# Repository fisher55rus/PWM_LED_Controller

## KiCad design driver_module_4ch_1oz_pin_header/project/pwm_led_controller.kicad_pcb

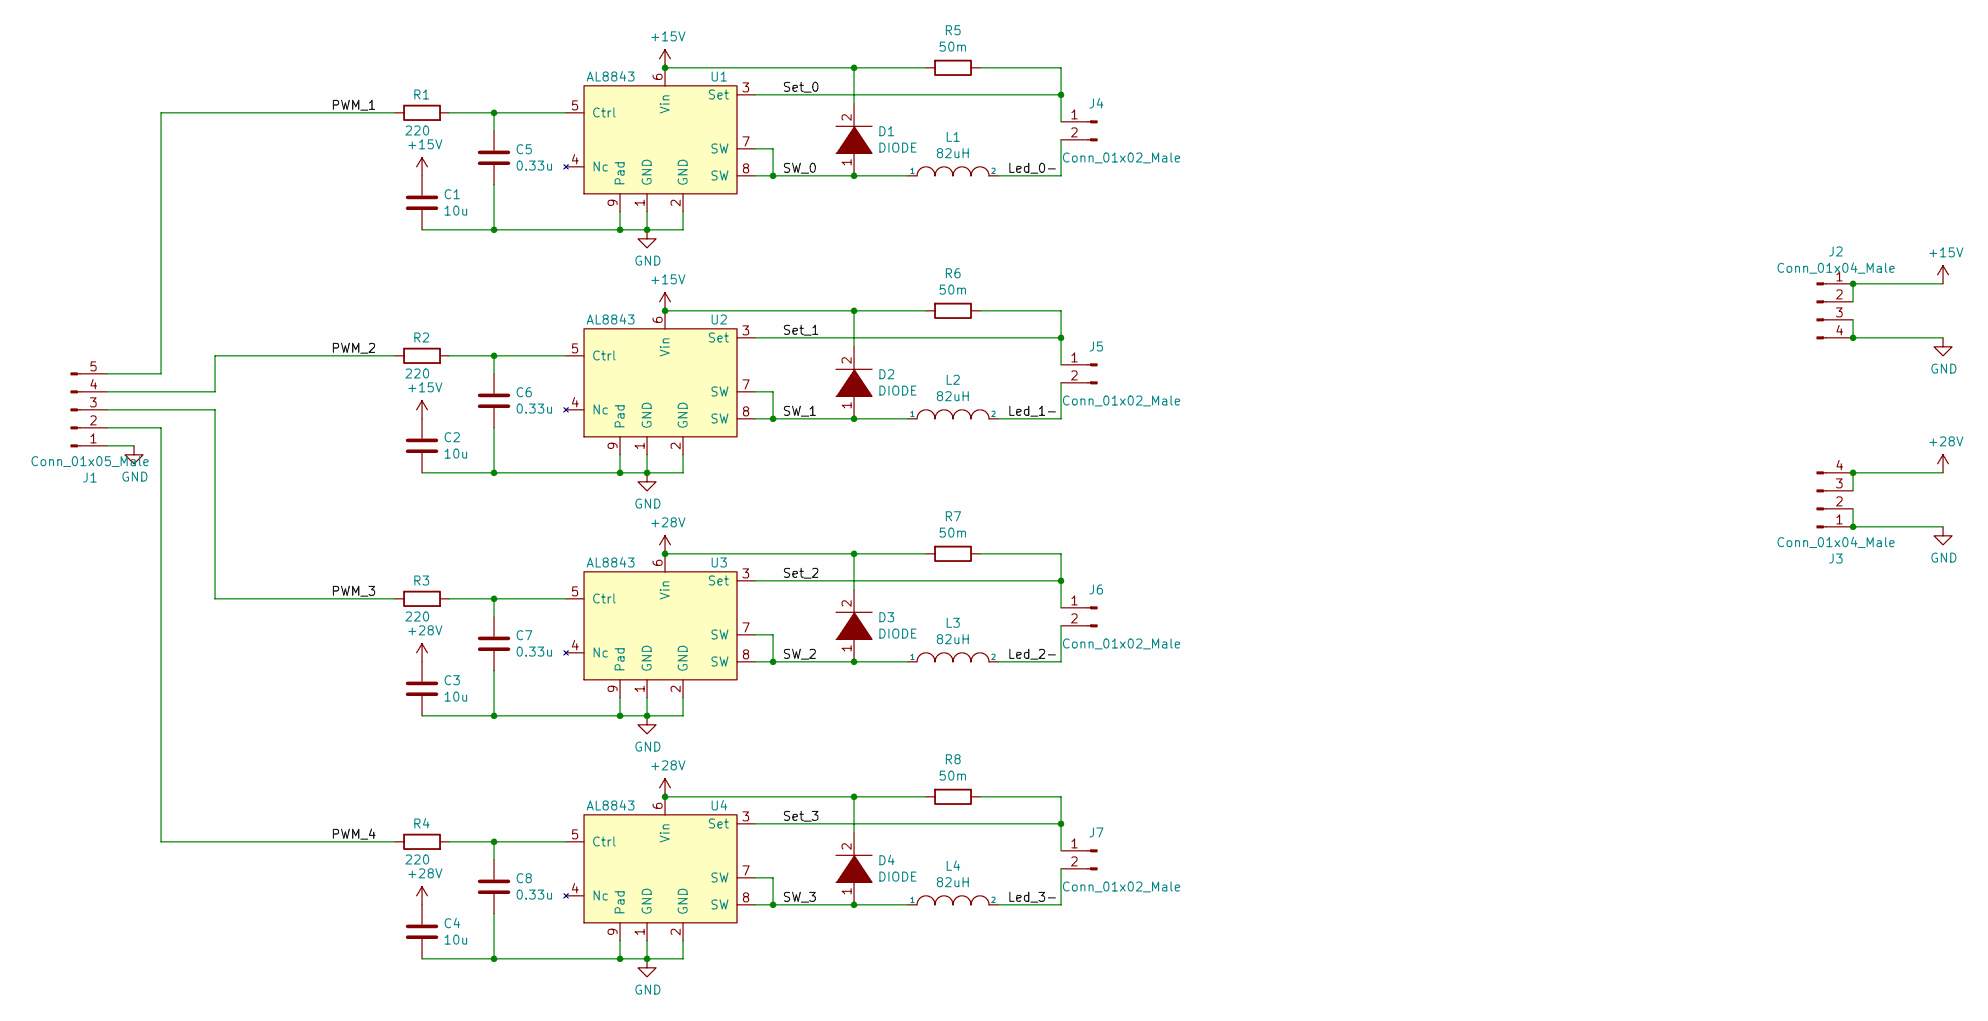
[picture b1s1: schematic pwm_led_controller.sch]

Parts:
C1, C2, C3, C4: 10u; C_1206_3216Metric_Pad1.42x1.75mm_HandSolder
C5, C6, C7, C8: 0.33u; C_0603_1608Metric_Pad1.05x0.95mm_HandSolder
D1, D2, D3, D4: DIODE; D_SMB_Handsoldering
J1: Conn_01x05_Male; PinHeader_1x05_P2.54mm_Vertical
J2, J3: Conn_01x04_Male; PinHeader_1x04_P2.54mm_Vertical
J4, J5, J6, J7: Conn_01x02_Male; PinHeader_1x02_P2.54mm_Vertical
L1, L2, L3, L4: 82uH; Package_2-smd_10.7x10mm
R1, R2, R3, R4: 220; R_0603_1608Metric_Pad1.05x0.95mm_HandSolder
R5, R6, R7, R8: 50m; R_1210_3225Metric_Pad1.42x2.65mm_HandSolder
U1, U2, U3, U4: AL8843; Diodes_PSOP-8

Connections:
+15V: C1.1, C2.1, D1.2 (A), D2.2 (A), J2.1, J2.2, R5.2, R6.2, U1.6 (Vin), U2.6 (Vin)
+28V: C3.1, C4.1, D3.2 (A), D4.2 (A), J3.3, J3.4, R7.2, R8.2, U3.6 (Vin), U4.6 (Vin)
/Led_0-: J4.2, L1.2
/Led_1-: J5.2, L2.2
/Led_2-: J6.2, L3.2
/Led_3-: J7.2, L4.2
/PWM_1: J1.5, R1.1
/PWM_2: J1.4, R2.1
/PWM_3: J1.3, R3.1
/PWM_4: J1.2, R4.1
/SW_0: D1.1 (K), L1.1, U1.7 (SW), U1.8 (SW)
/SW_1: D2.1 (K), L2.1, U2.7 (SW), U2.8 (SW)
/SW_2: D3.1 (K), L3.1, U3.7 (SW), U3.8 (SW)
/SW_3: D4.1 (K), L4.1, U4.7 (SW), U4.8 (SW)
/Set_0: J4.1, R5.1, U1.3 (Set)
/Set_1: J5.1, R6.1, U2.3 (Set)
/Set_2: J6.1, R7.1, U3.3 (Set)
/Set_3: J7.1, R8.1, U4.3 (Set)
GND: C1.2, C2.2, C3.2, C4.2, C5.2, C6.2, C7.2, C8.2, J1.1, J2.3, J2.4, J3.1, J3.2, U1.1 (GND), U1.2 (GND), U1.9 (Pad), U2.1 (GND), U2.2 (GND), U2.9 (Pad), U3.1 (GND), U3.2 (GND), U3.9 (Pad), U4.1 (GND), U4.2 (GND), U4.9 (Pad)
unnamed: C5.1, R1.2, U1.5 (Ctrl)
unnamed: C6.1, R2.2, U2.5 (Ctrl)
unnamed: C7.1, R3.2, U3.5 (Ctrl)
unnamed: C8.1, R4.2, U4.5 (Ctrl)

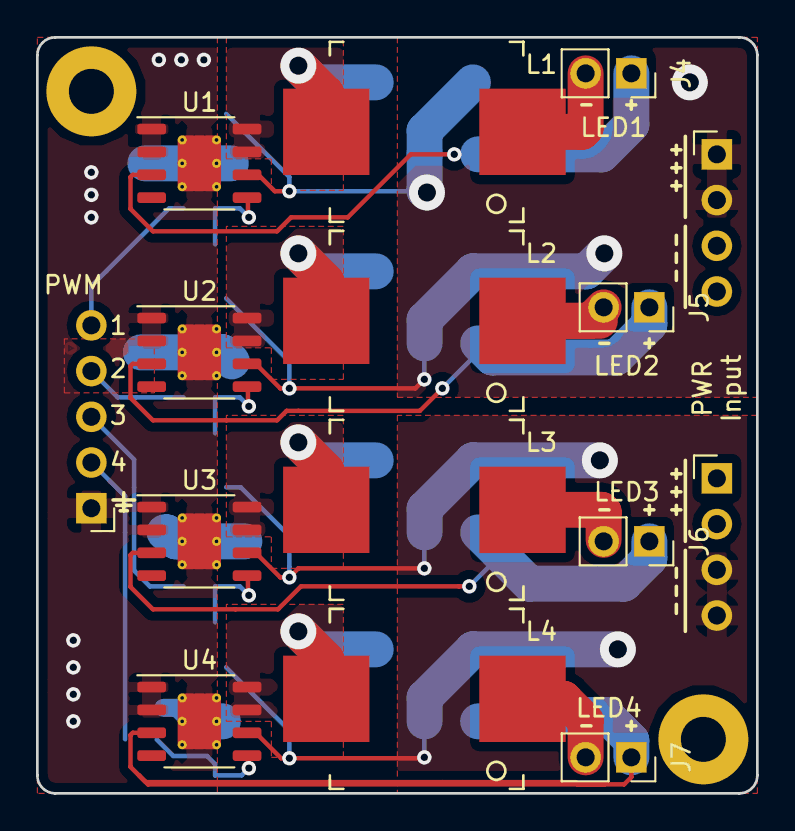
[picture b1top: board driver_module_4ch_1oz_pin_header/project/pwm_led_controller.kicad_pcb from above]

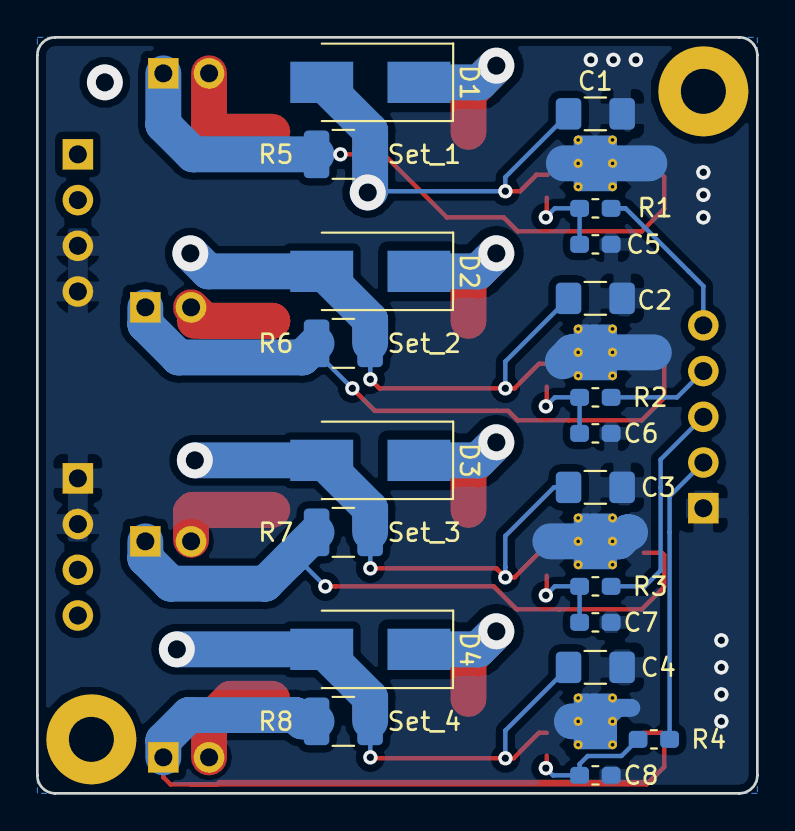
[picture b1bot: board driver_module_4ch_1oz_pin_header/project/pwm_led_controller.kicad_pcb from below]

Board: 2 copper layers, 40.0 x 42.0 mm, 35 parts (20 on the bottom side), 23 nets.

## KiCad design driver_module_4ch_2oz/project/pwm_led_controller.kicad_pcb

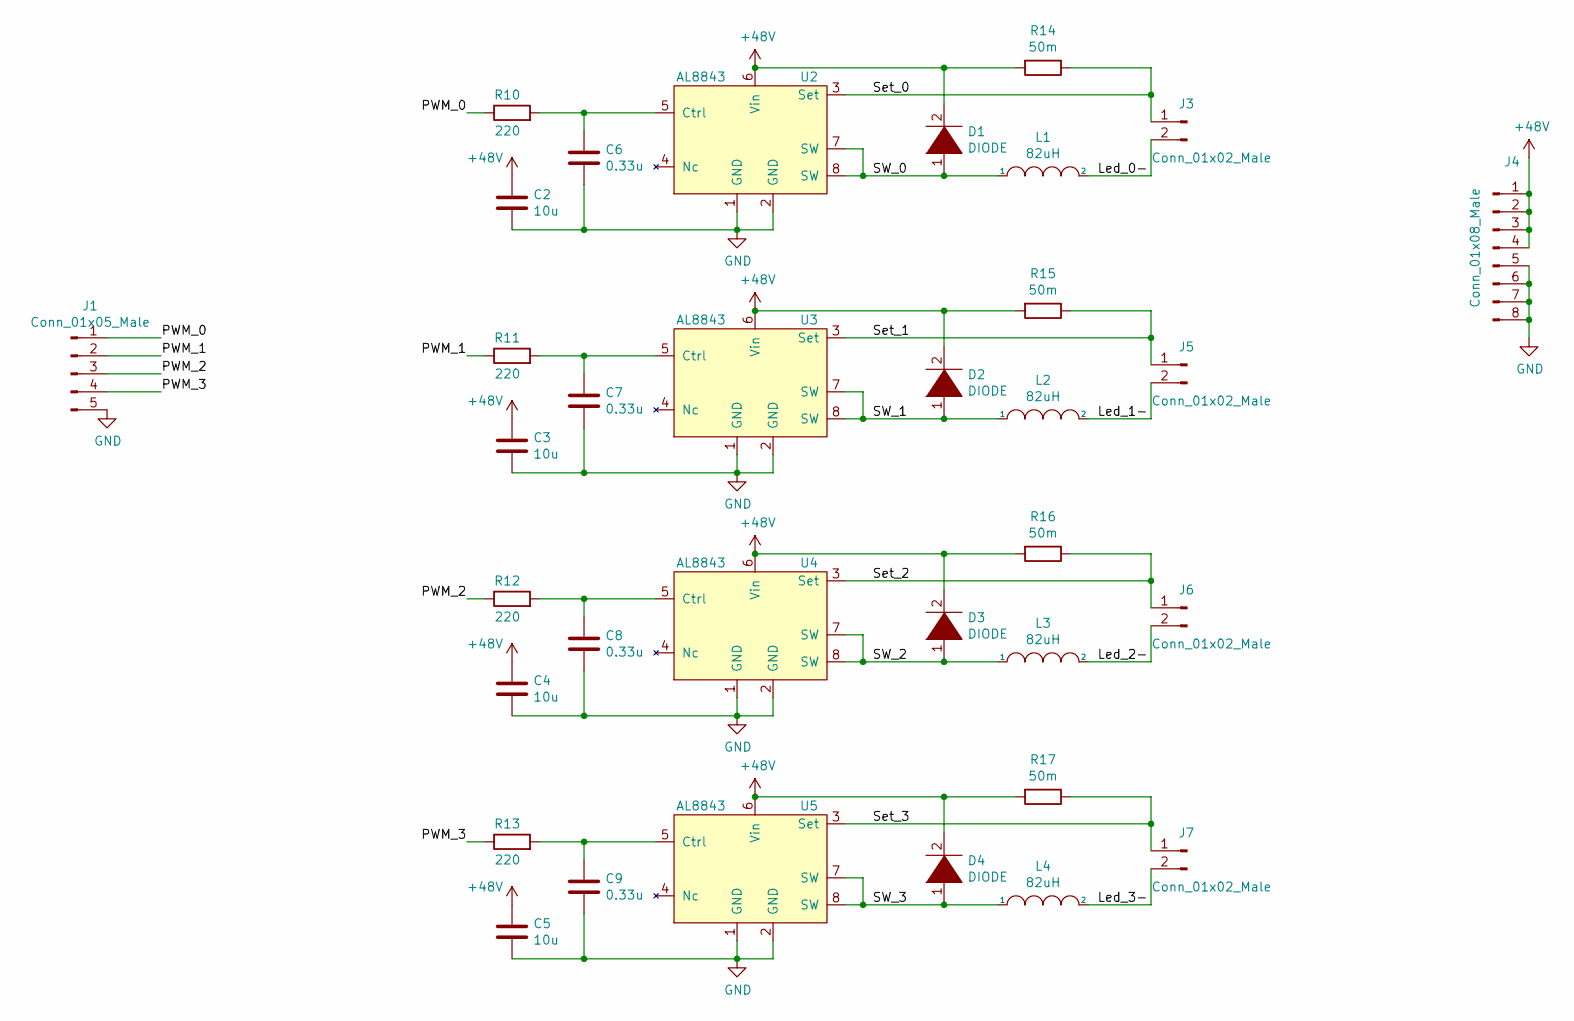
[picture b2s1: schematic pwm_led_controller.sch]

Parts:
C2, C3, C4, C5: 10u; C_1206_3216Metric_Pad1.42x1.75mm_HandSolder
C6, C7, C8, C9: 0.33u; C_0603_1608Metric_Pad1.05x0.95mm_HandSolder
D1, D2, D3, D4: DIODE; D_SMB-SMC_Universal_Handsoldering
J1: Conn_01x05_Male; PinHeader_1x05_P2.54mm_Vertical
J3, J5, J6, J7: Conn_01x02_Male; PinHeader_1x02_P2.54mm_Vertical
J4: Conn_01x08_Male; PinHeader_1x08_P2.54mm_Vertical
L1, L2, L3, L4: 82uH; L_Vishay_IDCS-7328
R10, R11, R12, R13: 220; R_0603_1608Metric_Pad1.05x0.95mm_HandSolder
R14, R15, R16, R17: 50m; R_1210_3225Metric_Pad1.42x2.65mm_HandSolder
U2, U3, U4, U5: AL8843; Diodes_PSOP-8

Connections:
+48V: C2.1, C3.1, C4.1, C5.1, D1.2 (A), D2.2 (A), D3.2 (A), D4.2 (A), J4.1, J4.2, J4.3, J4.4, R14.2, R15.2, R16.2, R17.2, U2.6 (Vin), U3.6 (Vin), U4.6 (Vin), U5.6 (Vin)
/Led_0-: J3.2, L1.2
/Led_1-: J5.2, L2.2
/Led_2-: J6.2, L3.2
/Led_3-: J7.2, L4.2
/PWM_0: J1.1, R10.1
/PWM_1: J1.2, R11.1
/PWM_2: J1.3, R12.1
/PWM_3: J1.4, R13.1
/SW_0: D1.1 (K), L1.1, U2.7 (SW), U2.8 (SW)
/SW_1: D2.1 (K), L2.1, U3.7 (SW), U3.8 (SW)
/SW_2: D3.1 (K), L3.1, U4.7 (SW), U4.8 (SW)
/SW_3: D4.1 (K), L4.1, U5.7 (SW), U5.8 (SW)
/Set_0: J3.1, R14.1, U2.3 (Set)
/Set_1: J5.1, R15.1, U3.3 (Set)
/Set_2: J6.1, R16.1, U4.3 (Set)
/Set_3: J7.1, R17.1, U5.3 (Set)
GND: C2.2, C3.2, C4.2, C5.2, C6.2, C7.2, C8.2, C9.2, J1.5, J4.5, J4.6, J4.7, J4.8, U2.1 (GND), U2.2 (GND), U3.1 (GND), U3.2 (GND), U4.1 (GND), U4.2 (GND), U5.1 (GND), U5.2 (GND)
unnamed: C6.1, R10.2, U2.5 (Ctrl)
unnamed: C7.1, R11.2, U3.5 (Ctrl)
unnamed: C8.1, R12.2, U4.5 (Ctrl)
unnamed: C9.1, R13.2, U5.5 (Ctrl)

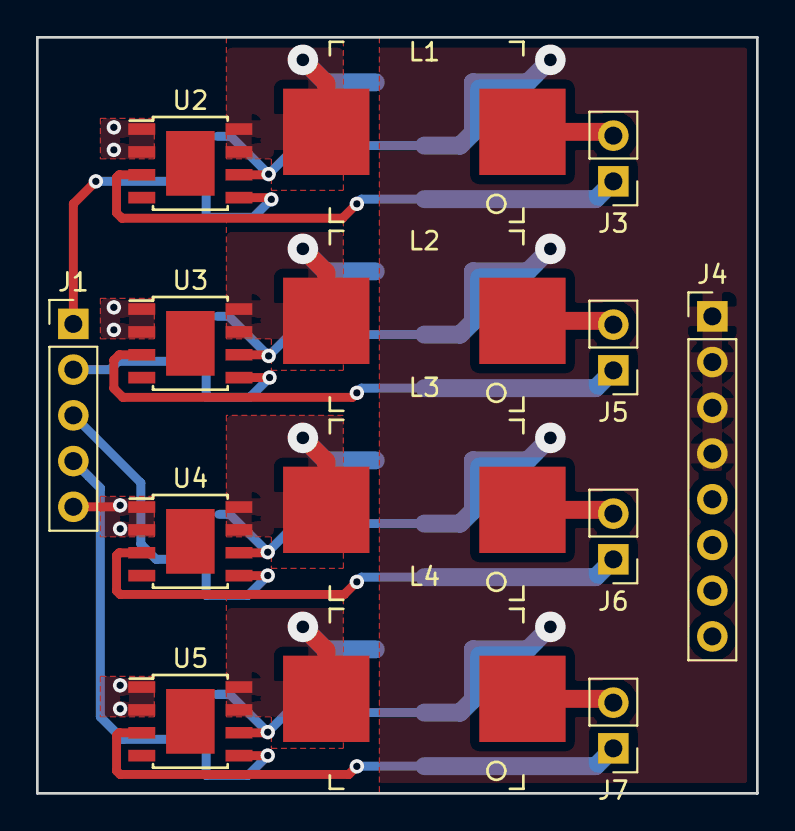
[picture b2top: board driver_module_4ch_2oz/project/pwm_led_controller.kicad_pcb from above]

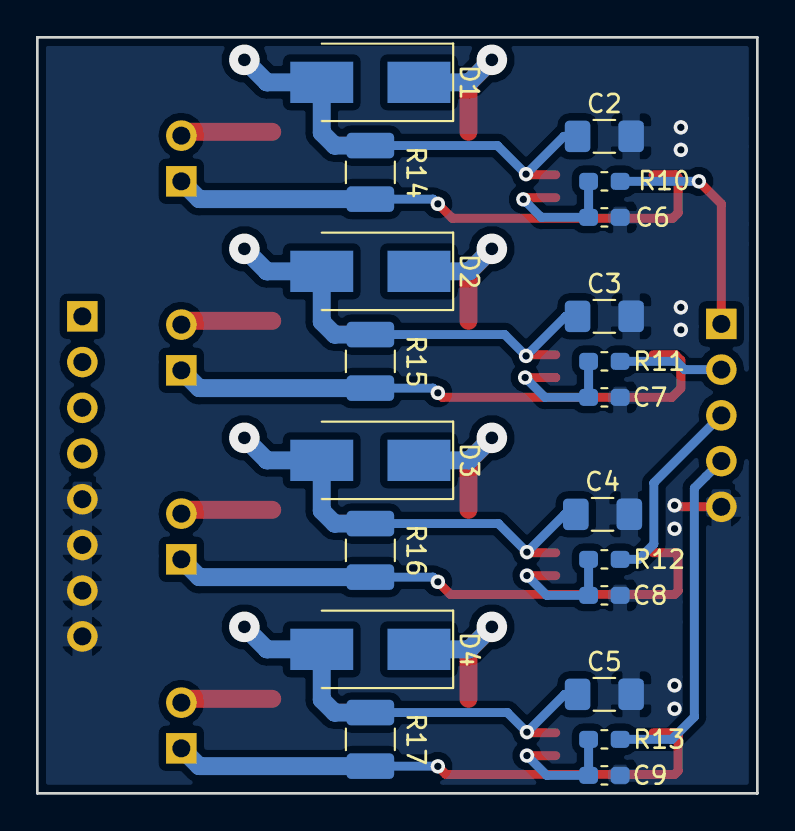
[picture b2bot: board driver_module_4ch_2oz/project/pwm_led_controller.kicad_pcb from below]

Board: 2 copper layers, 40.0 x 42.0 mm, 34 parts (20 on the bottom side), 22 nets.

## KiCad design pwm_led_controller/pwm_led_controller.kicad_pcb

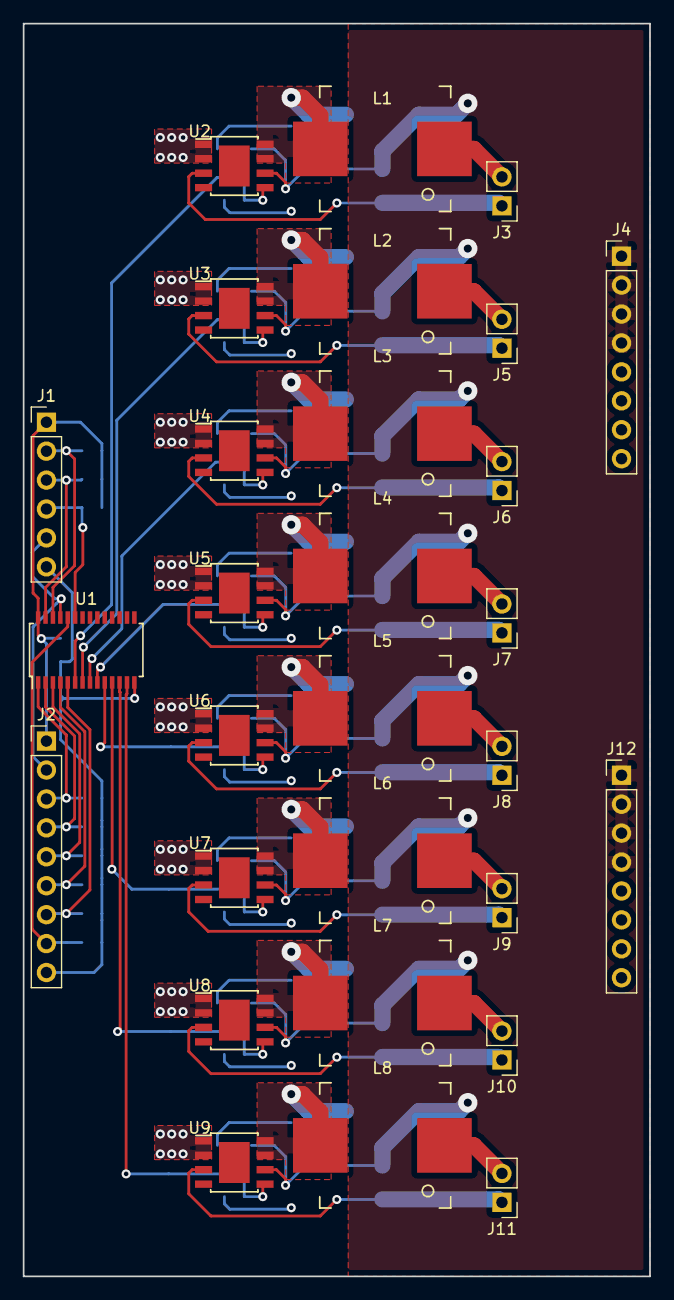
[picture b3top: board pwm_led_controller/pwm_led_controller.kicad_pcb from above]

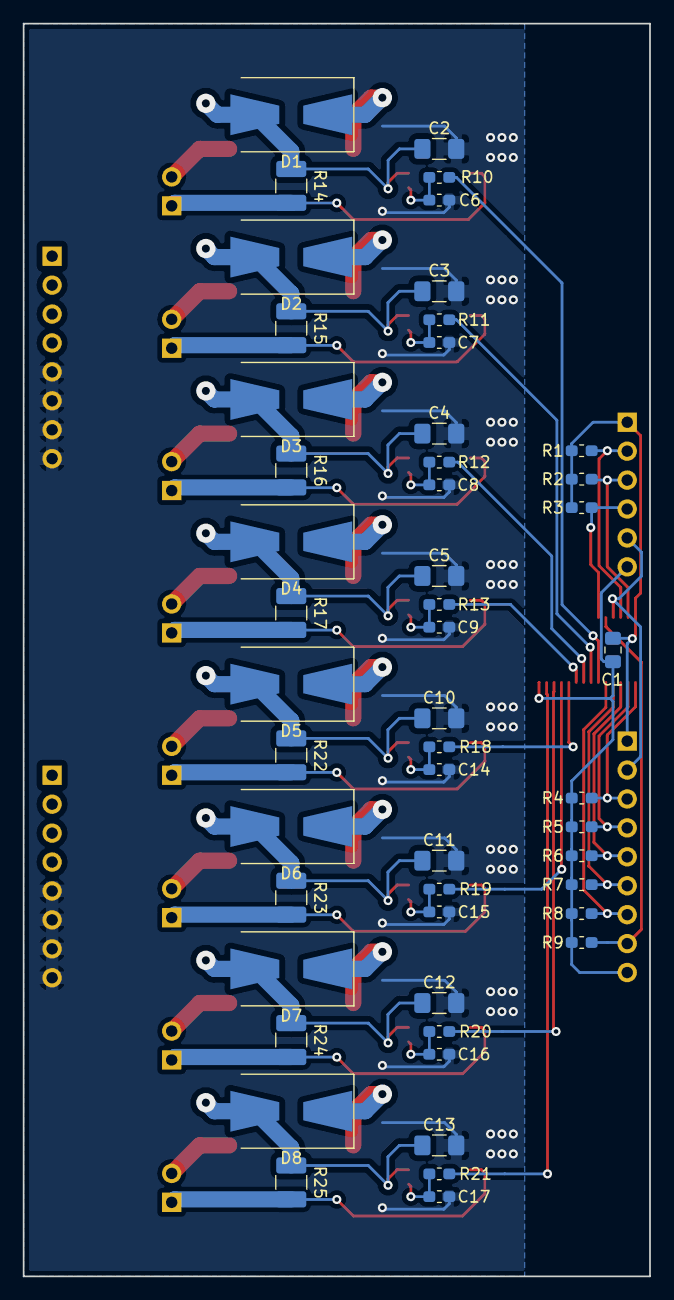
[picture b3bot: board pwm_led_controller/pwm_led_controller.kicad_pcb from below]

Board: 2 copper layers, 55.0 x 110.0 mm, 79 parts (50 on the bottom side), 54 nets.

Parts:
C1: 10u; C_0805_2012Metric_Pad1.15x1.40mm_HandSolder
C2, C3, C4, C5, C10, C11, C12, C13: 10u; C_1206_3216Metric_Pad1.42x1.75mm_HandSolder
C6, C7, C8, C9, C14, C15, C16, C17: 0.33u; C_0603_1608Metric_Pad1.05x0.95mm_HandSolder
D1, D2, D3, D4, D5, D6, D7, D8: DIODE; D_SMB-SMC_Universal_Handsoldering
J1: Conn_01x06_Male; PinHeader_1x06_P2.54mm_Vertical
J2: Conn_01x09_Male; PinHeader_1x09_P2.54mm_Vertical
J3, J5, J6, J7, J8, J9, J10, J11: Conn_01x02_Male; PinHeader_1x02_P2.54mm_Vertical
J4, J12: Conn_01x08_Male; PinHeader_1x08_P2.54mm_Vertical
L1, L2, L3, L4, L5, L6, L7, L8: 82uH; Package_2-smd_10.7x10mm
R1, R2, R3, R4, R5, R6, R7, R8, R9: 10k; R_0603_1608Metric_Pad1.05x0.95mm_HandSolder
R10, R11, R12, R13, R18, R19, R20, R21: 220; R_0603_1608Metric_Pad1.05x0.95mm_HandSolder
R14, R15, R16, R17, R22, R23, R24, R25: 50m; R_1210_3225Metric_Pad1.42x2.65mm_HandSolder
U1: PCA9685PW; TSSOP-28_4.4x9.7mm_P0.65mm
U2, U3, U4, U5, U6, U7, U8, U9: AL8843; Diodes_PSOP-8

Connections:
+48V: C2.1, C3.1, C4.1, C5.1, C10.1, C11.1, C12.1, C13.1, D1.2, D2.2, D3.2, D4.2, D5.2, D6.2, D7.2, D8.2, J4.1, J4.2, J4.3, J4.4, J12.1, J12.2, J12.3, J12.4, R14.2, R15.2, R16.2, R17.2, R22.2, R23.2, R24.2, R25.2, U2.6, U3.6, U4.6, U5.6, U6.6, U7.6, U8.6, U9.6
/A0: J2.3, R4.1, U1.1
/A1: J2.4, R5.1, U1.2
/A2: J2.5, R6.1, U1.3
/A3: J2.6, R7.1, U1.4
/A4: J2.7, R8.1, U1.5
/A5: J2.8, R9.1, U1.24
/CDA: J1.3, R2.2, U1.27
/CLK: J1.5, J2.2, U1.25
/Ground-On: J1.4, R3.2, U1.23
/Led_0-: J3.2, L1.2
/Led_1-: J5.2, L2.2
/Led_2-: J6.2, L3.2
/Led_3-: J7.2, L4.2
/Led_4-: J8.2, L5.2
/Led_5-: J9.2, L6.2
/Led_6-: J10.2, L7.2
/Led_7-: J11.2, L8.2
/PWM_0: R10.1, U1.6
/PWM_1: R11.1, U1.7
/PWM_2: R12.1, U1.8
/PWM_3: R13.1, U1.9
/PWM_4: R18.1, U1.10
/PWM_5: R19.1, U1.11
/PWM_6: R20.1, U1.12
/PWM_7: R21.1, U1.13
/SCL: J1.2, R1.2, U1.26
/SW_0: D1.1, L1.1, U2.7, U2.8
/SW_1: D2.1, L2.1, U3.7, U3.8
/SW_2: D3.1, L3.1, U4.7, U4.8
/SW_3: D4.1, L4.1, U5.7, U5.8
/SW_4: D5.1, L5.1, U6.7, U6.8
/SW_5: D6.1, L6.1, U7.7, U7.8
/SW_6: D7.1, L7.1, U8.7, U8.8
/SW_7: D8.1, L8.1, U9.7, U9.8
/Set_0: J3.1, R14.1, U2.3
/Set_1: J5.1, R15.1, U3.3
/Set_2: J6.1, R16.1, U4.3
/Set_3: J7.1, R17.1, U5.3
/Set_4: J8.1, R22.1, U6.3
/Set_5: J9.1, R23.1, U7.3
/Set_6: J10.1, R24.1, U8.3
/Set_7: J11.1, R25.1, U9.3
GND: C2.2, C3.2, C4.2, C5.2, C6.2, C7.2, C8.2, C9.2, C10.2, C11.2, C12.2, C13.2, C14.2, C15.2, C16.2, C17.2, J4.5, J4.6, J4.7, J4.8, J12.5, J12.6, J12.7, J12.8, U2.1, U2.2, U3.1, U3.2, U4.1, U4.2, U5.1, U5.2, U6.1, U6.2, U7.1, U7.2, U8.1, U8.2, U9.1, U9.2
unnamed: C6.1, R10.2, U2.5
unnamed: C7.1, R11.2, U3.5
unnamed: C8.1, R12.2, U4.5
unnamed: C9.1, R13.2, U5.5
unnamed: C14.1, R18.2, U6.5
unnamed: C15.1, R19.2, U7.5
unnamed: C16.1, R20.2, U8.5
unnamed: C17.1, R21.2, U9.5
VDD: C1.1, J1.1, J2.1, R1.1, R2.1, R3.1, U1.28
VSS: C1.2, J1.6, J2.9, R4.2, R5.2, R6.2, R7.2, R8.2, R9.2, U1.14

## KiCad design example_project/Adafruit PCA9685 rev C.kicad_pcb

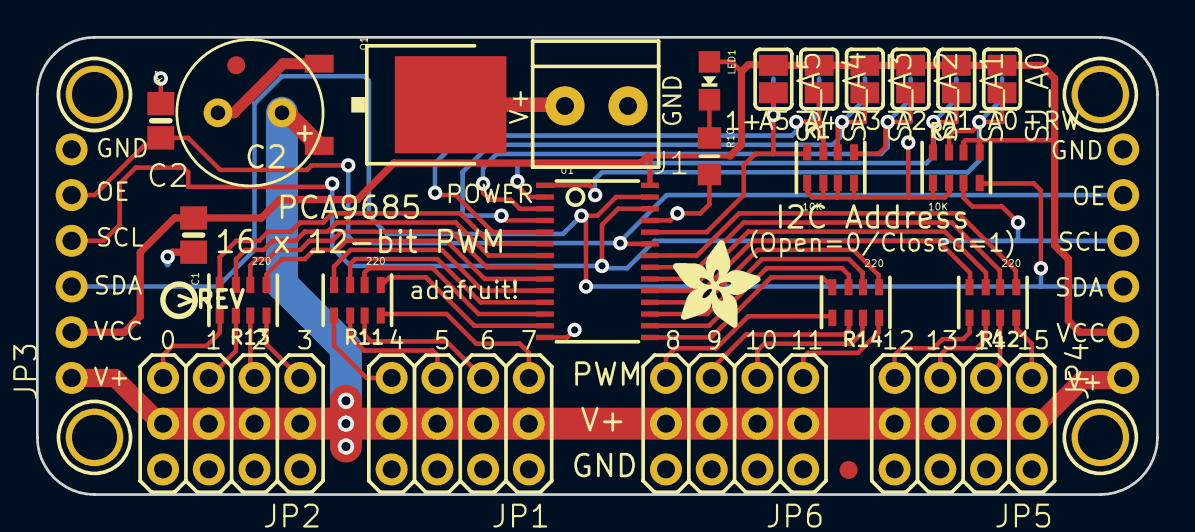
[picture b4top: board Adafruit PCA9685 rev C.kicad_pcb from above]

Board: 2 copper layers, 62.2 x 25.4 mm, 40 parts (0 on the bottom side), 46 nets.

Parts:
C1: 10uF; 0805-NO
C2: CPOL-USE3.5-8; E3,5-8
FID1, FID2: FIDUCIAL; FIDUCIAL_1MM
J1: TERMBLOCK_1X2; TERMBLOCK_1X2-3.5MM
JP1, JP2, JP5, JP6: HEADER-3X04; 3X04
JP3, JP4: PINHD-1X6CB; 1X06-CLEANBIG
LED1: GREEN; CHIPLED_0805_NOOUTLINE
Q1: AOD417; TO252
R1, R2: 10K; RESPACK_4X0603
R7: 10K; 0805-NO
R10: 470; _0805MP
R11, R12, R13, R14: 220; RESPACK_4X0603
SJ_A0, SJ_A1, SJ_A2, SJ_A3, SJ_A4, SJ_A5: SOLDERJUMPERREFLOW_NOPASTE; SOLDERJUMPER_REFLOW_NOPASTE
TP1, TP2, TP3, TP4, TP5, TP6: TESTPOINTROUND1MM; TESTPOINT_ROUND_1MM
U1: PCA9685; TSSOP28
U$47, U$48, U$49, U$50: MOUNTINGHOLE2.5; MOUNTINGHOLE_2.5_PLATED
U$51: ADAFRUIT_5MM
U$54: PCBFEAT-REV-040

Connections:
5.0V: C2.+, JP1.2, JP1.5, JP1.8, JP1.11, JP2.2, JP2.5, JP2.8, JP2.11, JP3.1, JP4.1, JP5.2, JP5.5, JP5.8, JP5.11, JP6.2, JP6.5, JP6.8, JP6.11, Q1.2
/A0: R2.7, SJ_A0.2, TP6.P$1, U1.1
/A1: R2.8, SJ_A1.2, TP5.P$1, U1.2
/A2: R1.5, SJ_A2.2, TP4.P$1, U1.3
/A3: R1.6, SJ_A3.2, TP3.P$1, U1.4
/A4: R1.7, SJ_A4.2, TP2.P$1, U1.5
/A5: R1.8, SJ_A5.2, TP1.P$1, U1.24
/OE: JP3.5, JP4.5, R7.1, U1.23
/PWM0: R13.4, U1.6
/PWM1: R13.3, U1.7
/PWM2: R13.2, U1.8
/PWM3: R13.1, U1.9
/PWM4: R11.4, U1.10
/PWM5: R11.3, U1.11
/PWM6: R11.2, U1.12
/PWM7: R11.1, U1.13
/PWM8: R14.4, U1.15
/PWM9: R14.3, U1.16
/PWM10: R14.2, U1.17
/PWM11: R14.1, U1.18
/PWM12: R12.4, U1.19
/PWM13: R12.3, U1.20
/PWM14: R12.2, U1.21
/PWM15: R12.1, U1.22
/SCL: JP3.4, JP4.4, R2.3, U1.26
/SDA: JP3.3, JP4.3, R2.4, U1.27
GND: C1.2, C2.-, J1.2, JP1.3, JP1.6, JP1.9, JP1.12, JP2.3, JP2.6, JP2.9, JP2.12, JP3.6, JP4.6, JP5.3, JP5.6, JP5.9, JP5.12, JP6.3, JP6.6, JP6.9, JP6.12, Q1.1, R1.1, R1.2, R1.3, R1.4, R2.1, R2.2, R7.2, R10.2, U1.14, U1.25
unnamed: J1.1, Q1.3
unnamed: JP1.1, R11.8
unnamed: JP1.4, R11.7
unnamed: JP1.7, R11.6
unnamed: JP1.10, R11.5
unnamed: JP2.1, R13.8
unnamed: JP2.4, R13.7
unnamed: JP2.7, R13.6
unnamed: JP2.10, R13.5
unnamed: JP5.1, R12.8
unnamed: JP5.4, R12.7
unnamed: JP5.7, R12.6
unnamed: JP5.10, R12.5
unnamed: JP6.1, R14.8
unnamed: JP6.4, R14.7
unnamed: JP6.7, R14.6
unnamed: JP6.10, R14.5
unnamed: LED1.C, R10.1
VCC: C1.1, JP3.2, JP4.2, LED1.A, R2.5, R2.6, SJ_A0.1, SJ_A1.1, SJ_A2.1, SJ_A3.1, SJ_A4.1, SJ_A5.1, U1.28

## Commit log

2019-03-24 First Steps
    - Example Project
    - Specs
    - Blocks
2019-03-25 Закончена схема, начата трассировка
2019-03-26 Разведена силовая часть
2019-03-26 Закончена трассировка
2019-04-02 Модуль с ШИМ, модуль драйверов
2019-04-05 Проект выполнен под установку светильника
2019-04-09 Подогнал расположение вилок под светодиодную плату
